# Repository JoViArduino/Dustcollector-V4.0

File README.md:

# Arduino Project: Dustcollector version 4 

Controlling dustcollecting system for multiple machines using valves. 

<p align="left" width="100%">

For every woodworker using lot of stationary machines it is important to remove the dust which is produced by using these machines. When one has many different machines, like table-saw, planer of a thicknesser one needs to connect all these machines. One needs to connect al these machies and includes valves so that only the dust of the machine which is used is collected. To achieve this one needs to include valves. This project allows you to install automatied valves which are controlled by Arduino''s. There is one Arduino for each manche. On them one and the same program can be installed. 
</p>

<br>
<sup> 
(The PCB for the project. An Arduino Uno is mounted under it while above there is an RS485 module. Here the PCB is placed on a test print of housing. Note the housing is only printer partially here, to see whether the PCB fits.)
</sup>

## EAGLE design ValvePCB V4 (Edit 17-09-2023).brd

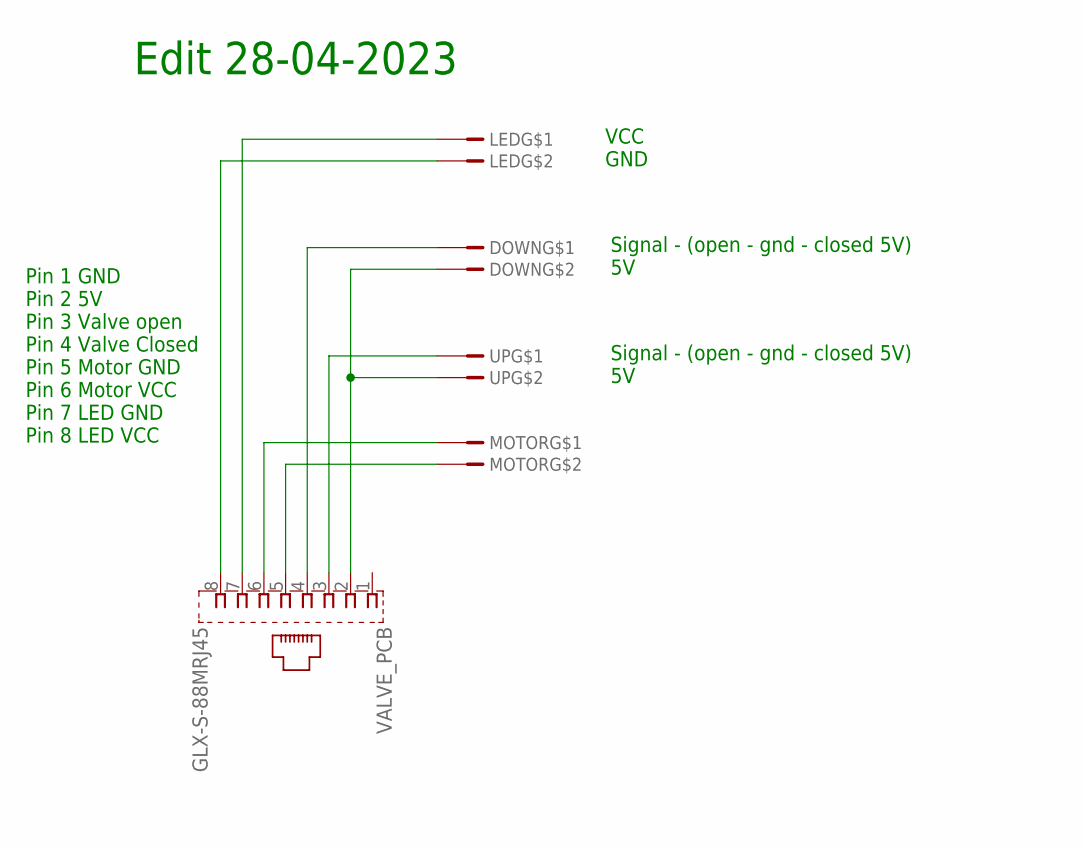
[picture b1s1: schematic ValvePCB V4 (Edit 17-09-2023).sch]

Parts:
DOWN: JST2; HDRV2W64P254_1X2_712X508X838B
LED: JST2; HDRV2W64P254_1X2_712X508X838B
MOTOR: JST2; HDRV2W64P254_1X2_712X508X838B
UP: JST2; HDRV2W64P254_1X2_712X508X838B
VALVE_PCB: GLX-S-88MRJ45; GLX-S-88M

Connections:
unnamed: MOTOR.1, VALVE_PCB.6
unnamed: MOTOR.2, VALVE_PCB.5
unnamed: UP.1, VALVE_PCB.3
unnamed: DOWN.2, UP.2, VALVE_PCB.2
unnamed: DOWN.1, VALVE_PCB.4
unnamed: LED.2, VALVE_PCB.8
unnamed: LED.1, VALVE_PCB.7

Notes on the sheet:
Pin 1 GND Pin 2 5V Pin 3 Valve open Pin 4 Valve Closed Pin 5 Motor GND Pin 6 Motor VCC Pin 7 LED GND Pin 8 LED VCC
Edit 28-04-2023
Signal - (open - gnd - closed 5V) 5V
VCC GND

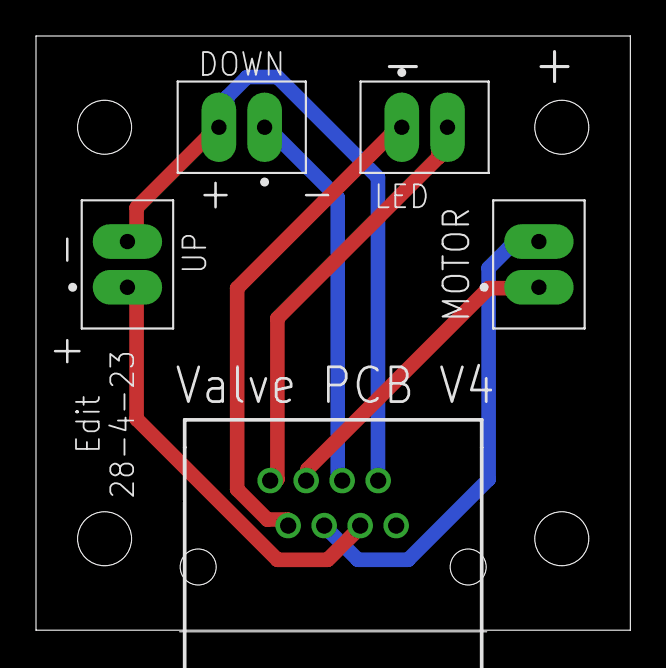
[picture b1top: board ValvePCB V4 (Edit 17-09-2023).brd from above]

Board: 2 copper layers, 33.0 x 33.1 mm, 5 parts (0 on the bottom side), 7 nets.

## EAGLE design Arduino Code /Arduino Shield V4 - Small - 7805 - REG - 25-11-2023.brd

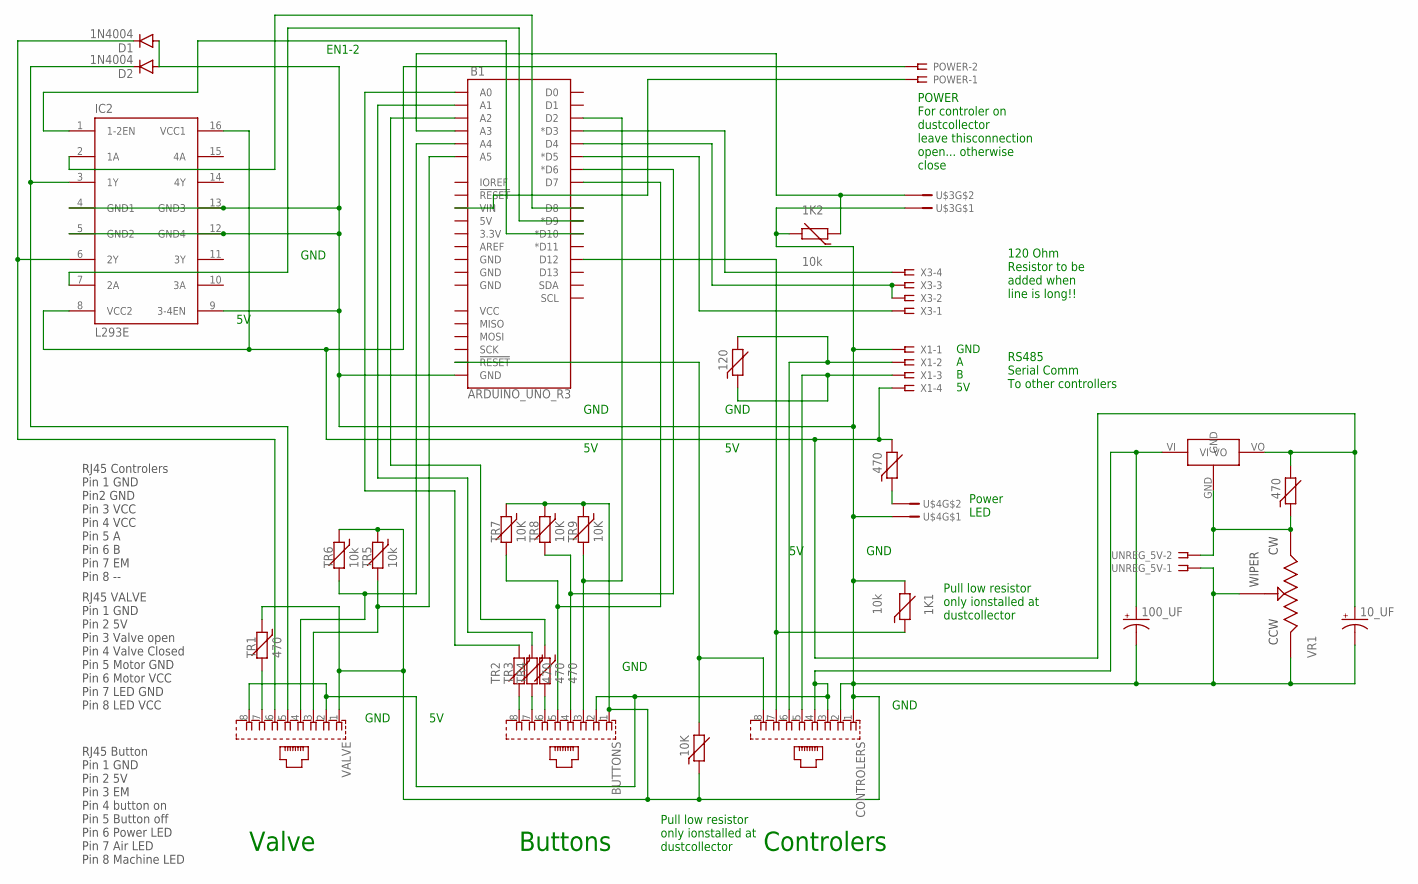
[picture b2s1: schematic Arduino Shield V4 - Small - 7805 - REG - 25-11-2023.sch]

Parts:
1K, 1K4: 470; R-7,5
1K1, 1K2: 10k; R-7,5
1K3: 120; R-7,5
10K: 10K; R-7,5
10_UF, 100_UF: CPOL-USE2,5-6E; E2,5-6E
B1: ARDUINO_UNO_R3; ARDUINO_R3
BUTTONS: GLX-S-88MRJ45; GLX-S-88M
CONTROLERS: GLX-S-88MRJ45; GLX-S-88M
D1, D2: 1N4004; DO41-10
IC2: L293E; DIL16
POWER: SSW-102-02-G-S
TR1, TR2, TR3, TR4: 470; R-7,5
TR5, TR6: 10k; R-7,5
TR7, TR8, TR9: 10K; R-7,5
U$1: 7805-TO220V; TO220AV
U$3, U$4: JST2; HDRV2W64P254_1X2_712X508X838B
UNREG_5V: SSW-102-02-G-S
VALVE: GLX-S-88MRJ45; GLX-S-88M
VR1: 3296W-1-103LF; W
X1, X3: SSW-104-02-G-S

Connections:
unnamed: 10K.2, B1.RESET@2 (!RESET!), CONTROLERS.8
unnamed: 1K1.1, B1.D12, CONTROLERS.7
unnamed: 1K3.2, CONTROLERS.6, X1.2
unnamed: 1K3.1, CONTROLERS.5, X1.3
unnamed: B1.A4, TR6.2, VALVE.4
unnamed: B1.D8, IC2.2 (1A)
unnamed: B1.D9 (*D9), IC2.7 (2A)
unnamed: D1.C, IC2.6 (2Y), VALVE.6
unnamed: D2.C, IC2.3 (1Y), VALVE.5
unnamed: TR1.2, VALVE.7
unnamed: BUTTONS.8, TR2.2
unnamed: 1K.1, U$4.2
unnamed: 1K2.1, B1.A3, U$3.2
unnamed: 1K1.2, 1K2.2, 10K.1, 10_UF.-, 100_UF.-, B1.GND@1 (GND), BUTTONS.1, CONTROLERS.1, CONTROLERS.2, D1.A, D2.A, IC2.4 (GND1), IC2.5 (GND2), IC2.9 (3-4EN), IC2.12 (GND4), IC2.13 (GND3), TR1.1, TR5.1, TR6.1, TR7.1, TR8.1, TR9.1, U$3.1, U$4.1, UNREG_5V.1, VALVE.1, VR1.1, VR1.2, X1.1
unnamed: B1.A1, TR3.1
unnamed: BUTTONS.7, TR3.2
unnamed: BUTTONS.6, TR4.2
unnamed: B1.A0, TR2.1
unnamed: B1.D10 (*D10), IC2.1 (1-2EN)
unnamed: B1.A2, TR4.1
unnamed: B1.D7, BUTTONS.5, TR7.2
unnamed: B1.D6 (*D6), BUTTONS.4, TR8.2
unnamed: B1.D2, BUTTONS.3, TR9.2
unnamed: B1.D3 (*D3), X3.4
unnamed: B1.D4, X3.2, X3.3
unnamed: B1.D5 (*D5), X3.1
unnamed: B1.A5, TR5.2, VALVE.3
unnamed: 1K4.1, U$1.GND, UNREG_5V.2, VR1.3
unnamed: B1.VIN, POWER.1
unnamed: 1K.2, 1K4.2, 10_UF.+, IC2.8 (VCC2), IC2.16 (VCC1), POWER.2, U$1.VO, X1.4
unnamed: 100_UF.+, BUTTONS.2, CONTROLERS.3, CONTROLERS.4, U$1.VI, VALVE.2, VALVE.8

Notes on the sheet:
GND
RJ45 VALVE Pin 1 GND Pin 2 5V Pin 3 Valve open Pin 4 Valve Closed Pin 5 Motor GND Pin 6 Motor VCC Pin 7 LED GND Pin 8 LED VCC
RJ45 Controlers Pin 1 GND Pin2 GND Pin 3 VCC Pin 4 VCC Pin 5 A Pin 6 B Pin 7 EM Pin 8 --
RJ45 Button Pin 1 GND Pin 2 5V Pin 3 EM Pin 4 button on Pin 5 Button off Pin 6 Power LED Pin 7 Air LED Pin 8 Machine LED
Buttons
Valve
Controlers
Pull low resistor only ionstalled at dustcollector
Power LED
RS485 Serial Comm To other controllers
GND A B 5V
120 Ohm Resistor to be added when line is long!!
POWER For controler on dustcollector leave thisconnection open... otherwise close
EN1-2

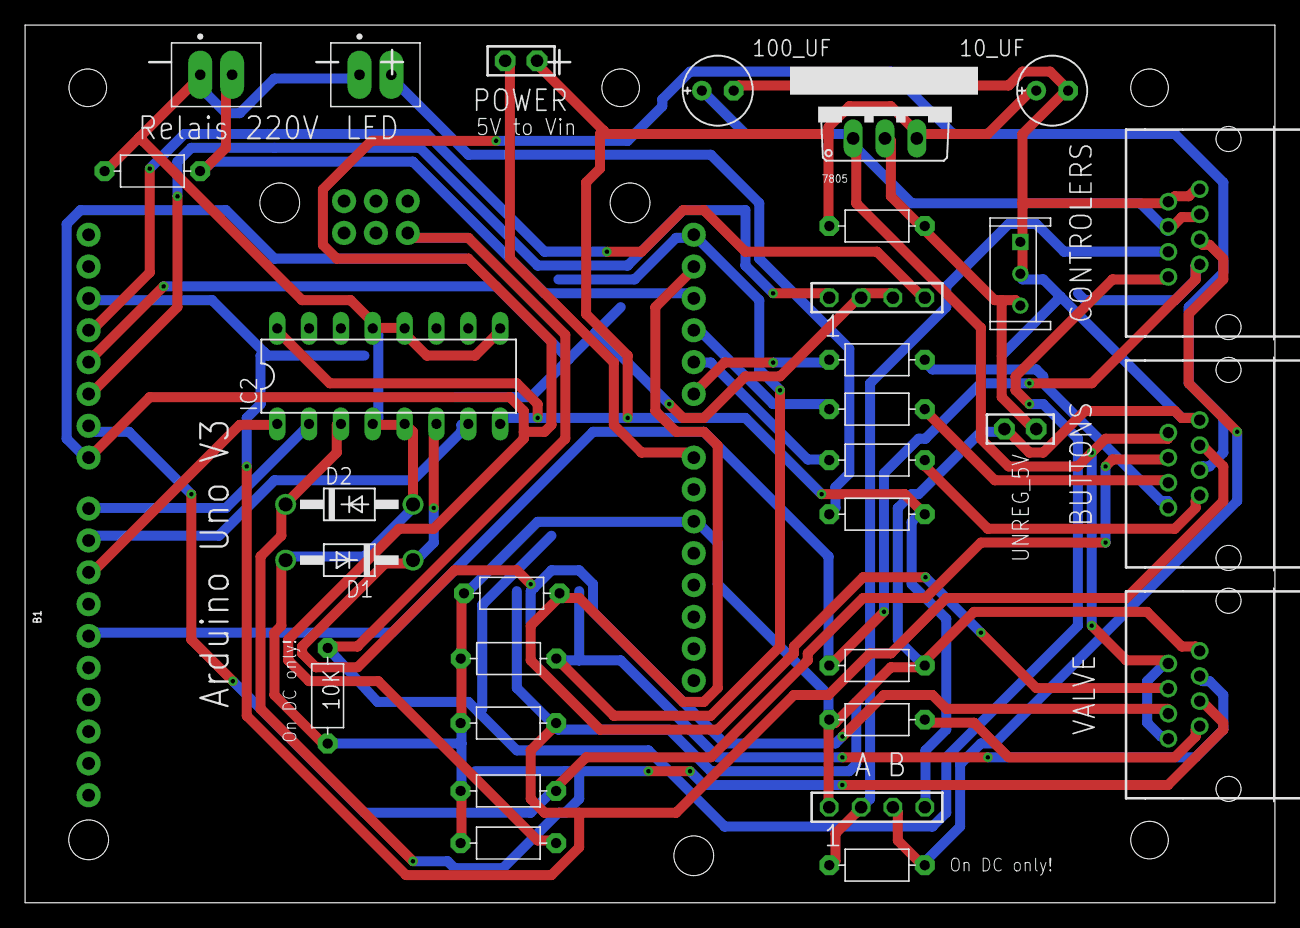
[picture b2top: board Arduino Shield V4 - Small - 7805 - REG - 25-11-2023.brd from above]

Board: 2 copper layers, 99.7 x 70.0 mm, 32 parts (0 on the bottom side), 31 nets.

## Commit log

2023-12-04 Rename Arduino Shield V4 - Small - 7805 - REG - 25-11-2023.brd to Arduino Code /Arduino Shield V4 - Small - 7805 - REG - 25-11-2023.brd

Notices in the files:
parts and their libraries:
SparkFun-Boards: Licensing: Creative Commons ShareAlike 4.0 International - https://creativecommons.org/licenses/by-sa/4.0
Volks73-Bourns: Creative Commons Attribution-ShareAlike 3.0 Unported (CC BY-SA 3.0), http://creativecommons.org/licenses/by-sa/3.0/.
